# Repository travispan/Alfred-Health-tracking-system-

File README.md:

# Alfred: Health Information tracking system (final year design project)

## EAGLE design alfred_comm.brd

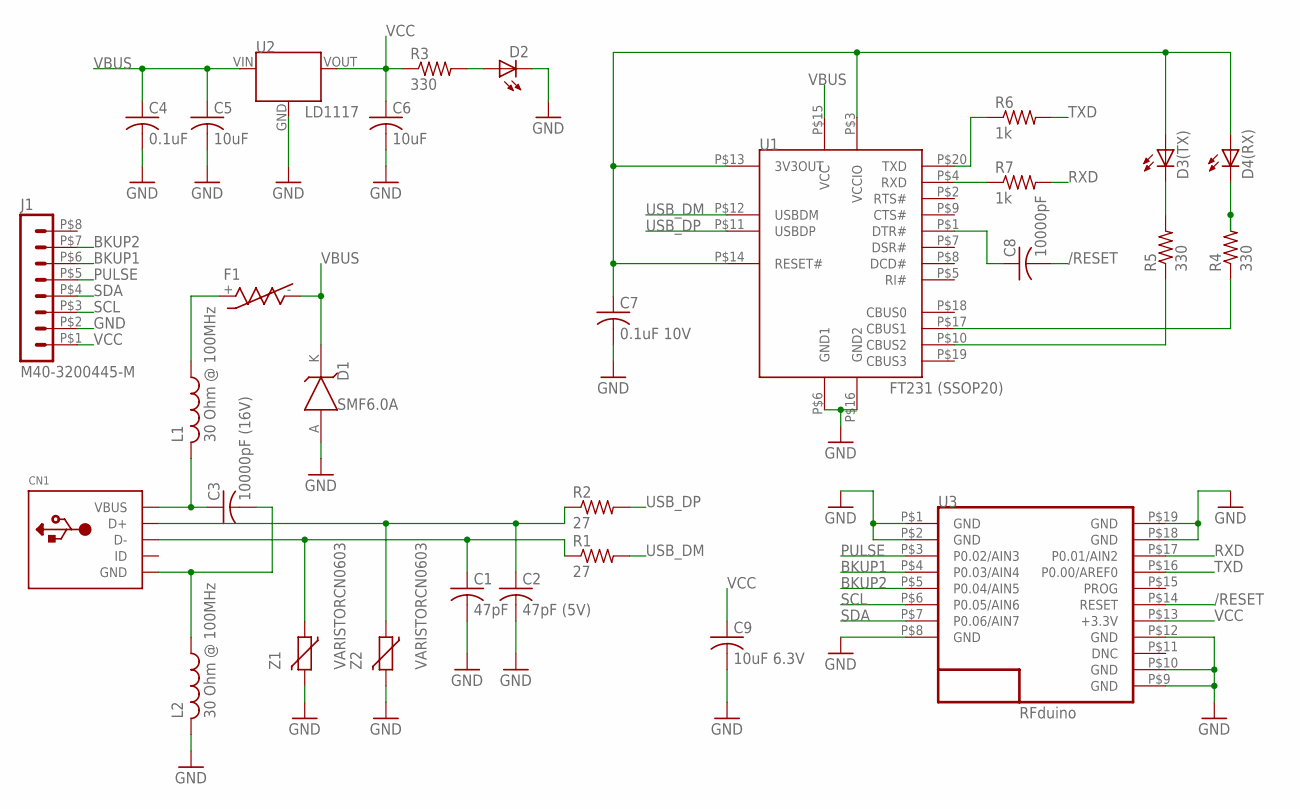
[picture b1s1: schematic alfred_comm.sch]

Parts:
C1: 47pF; C0603
C2: 47pF (5V); C0603
C3: 10000pF (16V); C0603
C4: 0.1uF; C0603
C5, C6: 10uF; C0603
C7: 0.1uF 10V; C0603
C8: 10000pF; C0603
C9: 10uF 6.3V; C0603
CN1: USBMINIB; USB-MINIB
D1: SMF6.0A; SOD-123F
D2, D3(TX), D4(RX): LEDCHIPLED_0603; CHIPLED_0603
F1: MF-MSMF050; BOURNS-STYLE1
J1: M40-3200445-M; 8-PO-M
L1, L2: 30 Ohm @ 100MHz; L0603
R1, R2: 27; R0603
R3, R4, R5: 330; R0603
R6, R7: 1k; R0603
U1: FT231; SSOP20
U2: LD1117-SOT-223; SOT223
U3: RFD22301; RFD21733
Z1, Z2: VARISTORCN0603; CT/CN0603

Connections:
/RESET: C8.2, U3.P$14 (RESET)
BKUP1: J1.P$6 (6), U3.P$4 (P0.03/AIN4)
BKUP2: J1.P$7 (7), U3.P$5 (P0.04/AIN5)
GND: C1.2, C2.2, C4.2, C5.2, C6.2, C7.2, C9.2, D1.A, D2.C, J1.P$2 (2), L2.2, U1.P$6 (GND1), U1.P$16 (GND2), U2.GND, U3.P$1 (GND), U3.P$2 (GND), U3.P$8 (GND), U3.P$9 (GND), U3.P$10 (GND), U3.P$12 (GND), U3.P$18 (GND), U3.P$19 (GND), Z1.2, Z2.2
unnamed: C2.1, CN1.D+, R2.1, Z2.1
unnamed: C1.1, CN1.D-, R1.1, Z1.1
unnamed: C3.1, CN1.VBUS, L1.2
unnamed: C3.2, CN1.GND, L2.1
unnamed: F1.+, L1.1
unnamed: C7.1, D3(TX).A, D4(RX).A, U1.P$3 (VCCIO), U1.P$13 (3V3OUT), U1.P$14 (RESET#)
unnamed: C8.1, U1.P$1 (DTR#)
unnamed: R4.1, U1.P$17 (CBUS1)
unnamed: D3(TX).C, R5.2
unnamed: D4(RX).C, R4.2
unnamed: R5.1, U1.P$10 (CBUS2)
unnamed: R6.1, U1.P$20 (TXD)
unnamed: R7.1, U1.P$4 (RXD)
unnamed: D2.A, R3.2
PULSE: J1.P$5 (5), U3.P$3 (P0.02/AIN3)
RXD: R7.2, U3.P$17 (P0.01/AIN2)
SCL: J1.P$3 (3), U3.P$6 (P0.05/AIN6)
SDA: J1.P$4 (4), U3.P$7 (P0.06/AIN7)
TXD: R6.2, U3.P$16 (P0.00/AREF0)
USB_DM: R1.2, U1.P$12 (USBDM)
USB_DP: R2.2, U1.P$11 (USBDP)
VBUS: C4.1, C5.1, D1.K, F1.-, U1.P$15 (VCC), U2.VIN (IN)
VCC: C6.1, C9.1, J1.P$1 (1), R3.1, U2.VOUT (OUT), U3.P$13 (+3.3V)

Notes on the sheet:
RFduino
FT231 (SSOP20)
LD1117
SMF6.0A

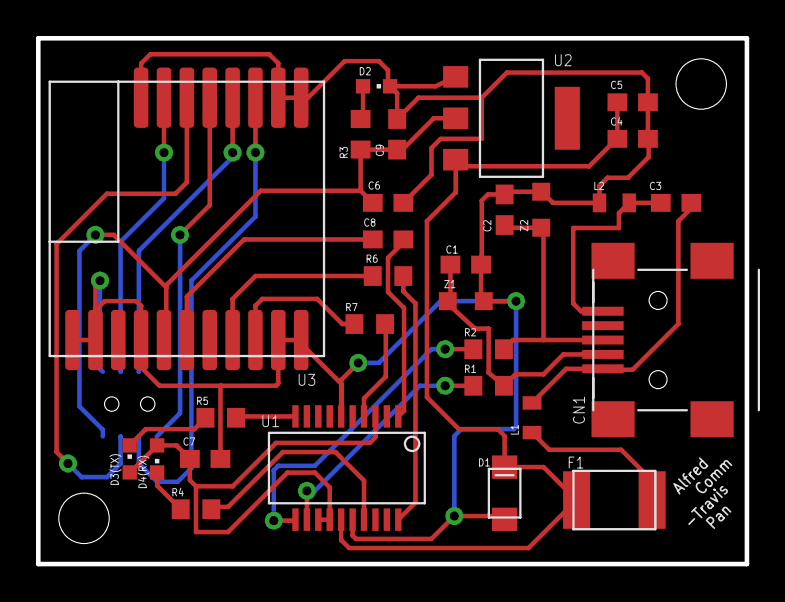
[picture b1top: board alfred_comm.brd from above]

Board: 2 copper layers, 39.4 x 29.2 mm, 30 parts (1 on the bottom side), 27 nets.

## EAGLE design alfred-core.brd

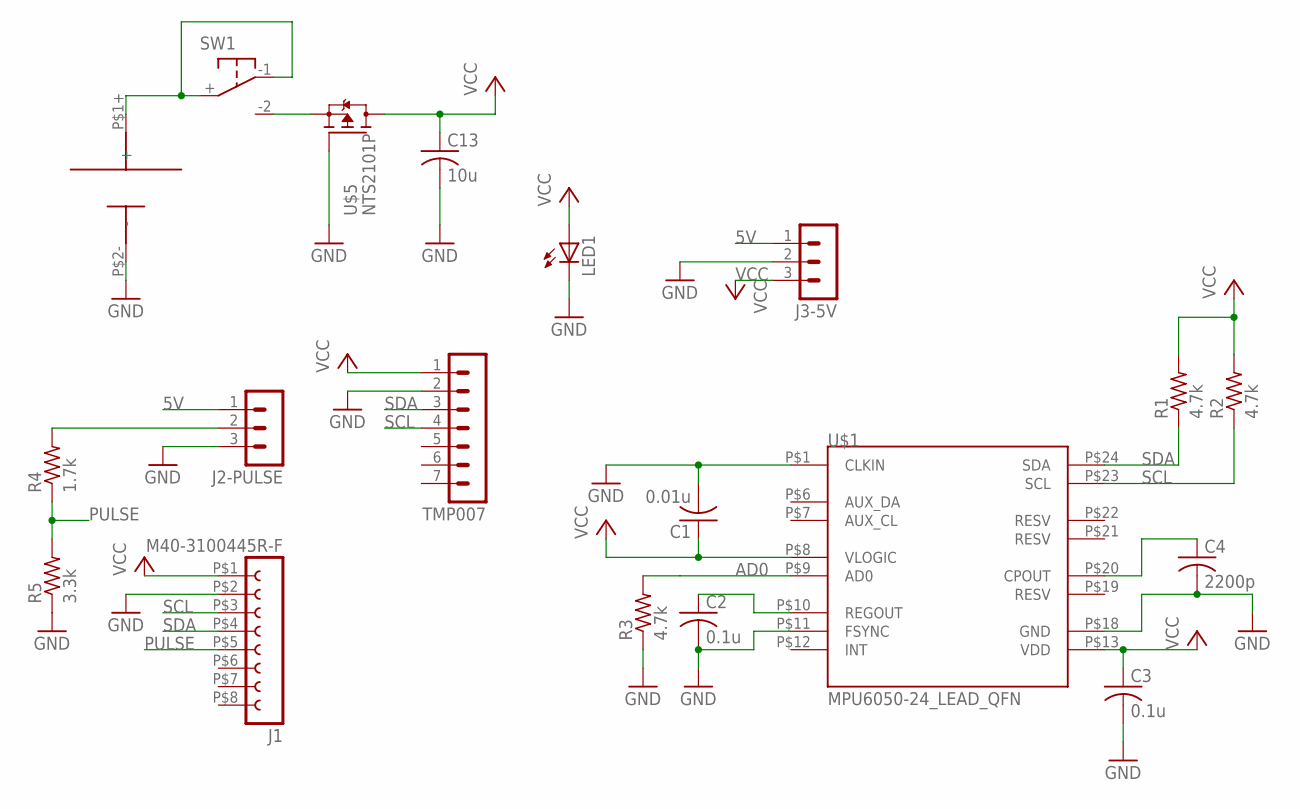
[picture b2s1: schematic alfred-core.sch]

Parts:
BAT1: CR2032HOLDER; CR2032-HOLDER
C1: 0.01u; C0603
C2, C3: 0.1u; C0603
C4: 2200p; C0603
C13: 10u; C0603
J1: M40-3100445R-F; 8-PO-F
J2-PULSE, J3-5V: MA03-1
LED1: LEDCHIPLED_0603; CHIPLED_0603
R1, R2, R3: 4.7k; R0603
R4: 1.7k; R0603
R5: 3.3k; R0603
SW1: JS102011SAQN
TMP007: MA07-1
U$1: MPU6050-24_LEAD_QFN; 24_LEAD_QFN(4X4X0.9)
U$5: NTS2101P; SOT323

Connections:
5V: J2-PULSE.1, J3-5V.1
AD0: R3.2, U$1.P$9 (AD0)
GND: BAT1.P$2- (-), C1.2, C2.2, C3.2, C4.2, C13.2, J1.P$2 (2), J2-PULSE.3, J3-5V.2, LED1.C, R3.1, R5.1, TMP007.2, U$1.P$1 (CLKIN), U$1.P$11 (FSYNC), U$1.P$18 (GND), U$5.G
unnamed: C2.1, U$1.P$10 (REGOUT)
unnamed: C4.1, U$1.P$20 (CPOUT)
unnamed: J2-PULSE.2, R4.2
unnamed: BAT1.P$1+ (+), SW1.+, SW1.-1
unnamed: SW1.-2, U$5.S
PULSE: J1.P$5 (5), R4.1, R5.2
SCL: J1.P$3 (3), R2.1, TMP007.4, U$1.P$23 (SCL)
SDA: J1.P$4 (4), R1.1, TMP007.3, U$1.P$24 (SDA)
VCC: C1.1, C3.1, C13.1, J1.P$1 (1), J3-5V.3, LED1.A, R1.2, R2.2, TMP007.1, U$1.P$8 (VLOGIC), U$1.P$13 (VDD), U$5.D

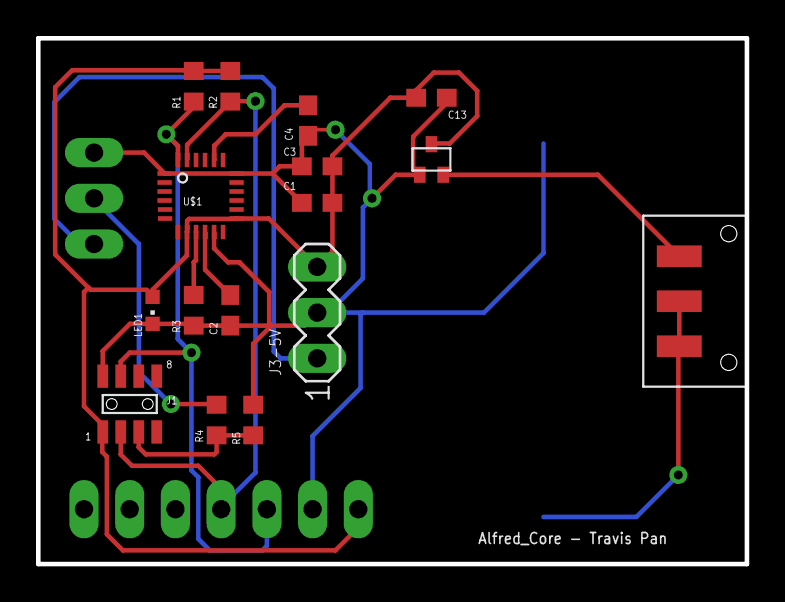
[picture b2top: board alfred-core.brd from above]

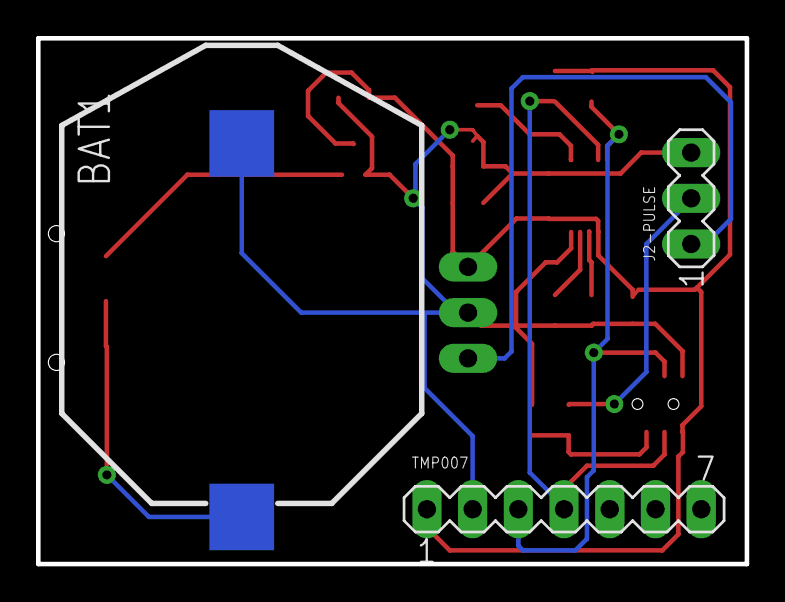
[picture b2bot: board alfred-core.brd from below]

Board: 2 copper layers, 39.4 x 29.2 mm, 19 parts (3 on the bottom side), 12 nets.

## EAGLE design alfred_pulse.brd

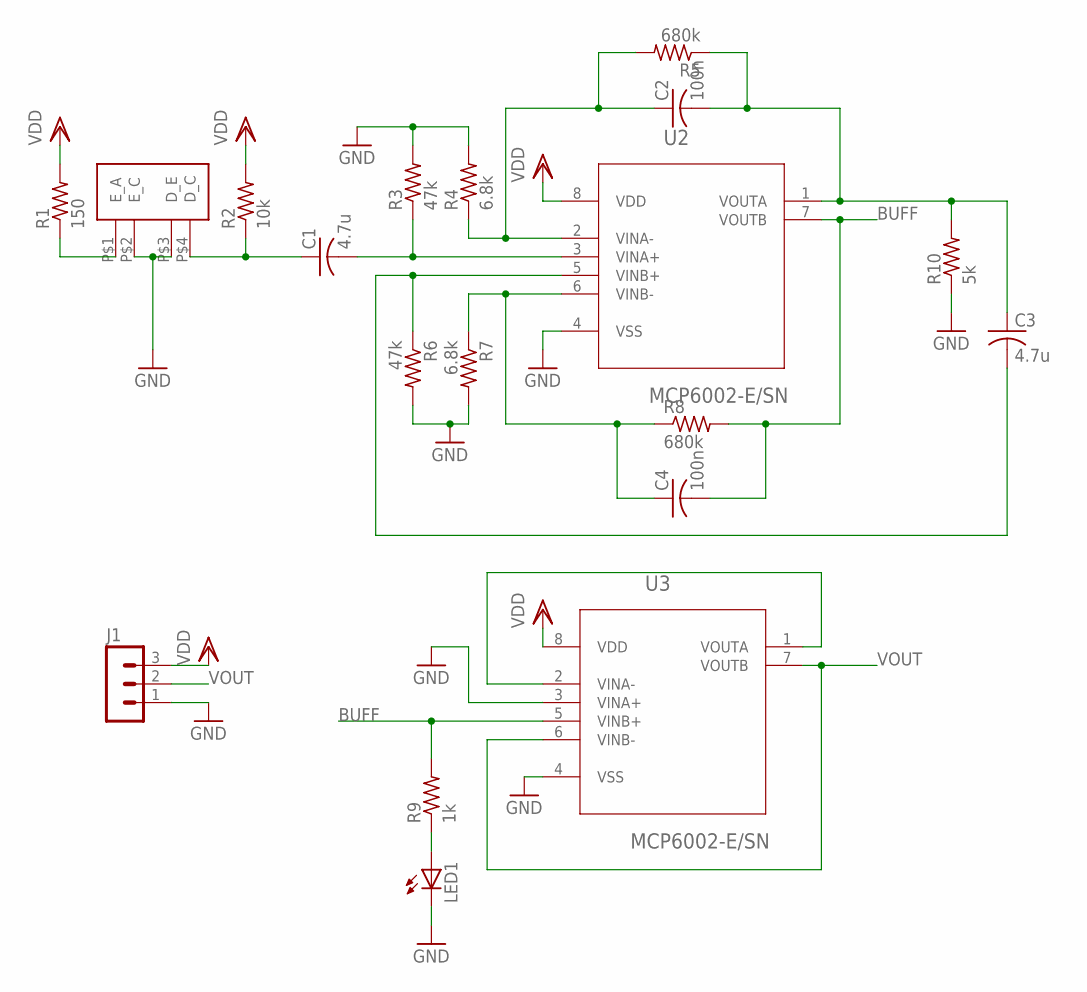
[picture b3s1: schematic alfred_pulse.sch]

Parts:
C1, C3: 4.7u; C0603
C2, C4: 100n; C0603
J1: MA03-1
LED1: LEDCHIPLED_1206; CHIPLED_1206
R1: 150; R0603
R2: 10k; R0603
R3, R6: 47k; R0603
R4, R7: 6.8k; R0603
R5, R8: 680k; R0603
R9: 1k; R0603
R10: 5k; R0603
U2, U3: MCP6002-E/SN; SOIC127P600X175-8N
U$1: TCRT1001

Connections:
BUFF: C4.2, R8.2, R9.2, U2.7 (VOUTB), U3.5 (VINB+)
GND: J1.1, LED1.C, R3.2, R4.2, R6.2, R7.2, R10.1, U2.4 (VSS), U3.3 (VINA+), U3.4 (VSS), U$1.P$2 (E_C), U$1.P$3 (D_E)
unnamed: R1.1, U$1.P$1 (E_A)
unnamed: C1.1, R2.1, U$1.P$4 (D_C)
unnamed: C1.2, R3.1, U2.3 (VINA+)
unnamed: C3.2, R6.1, U2.5 (VINB+)
unnamed: LED1.A, R9.1
unnamed: C4.1, R7.1, R8.1, U2.6 (VINB-)
unnamed: C2.2, C3.1, R5.1, R10.2, U2.1 (VOUTA)
unnamed: C2.1, R4.1, R5.2, U2.2 (VINA-)
unnamed: U3.1 (VOUTA), U3.2 (VINA-)
VDD: J1.3, R1.2, R2.2, U2.8 (VDD), U3.8 (VDD)
VOUT: J1.2, U3.6 (VINB-), U3.7 (VOUTB)

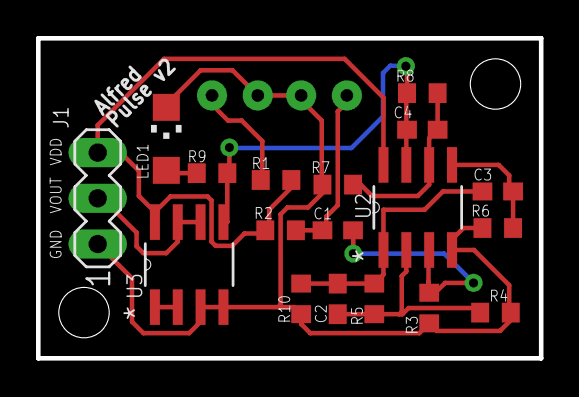
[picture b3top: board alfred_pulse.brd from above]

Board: 2 copper layers, 27.9 x 17.8 mm, 19 parts (1 on the bottom side), 13 nets.

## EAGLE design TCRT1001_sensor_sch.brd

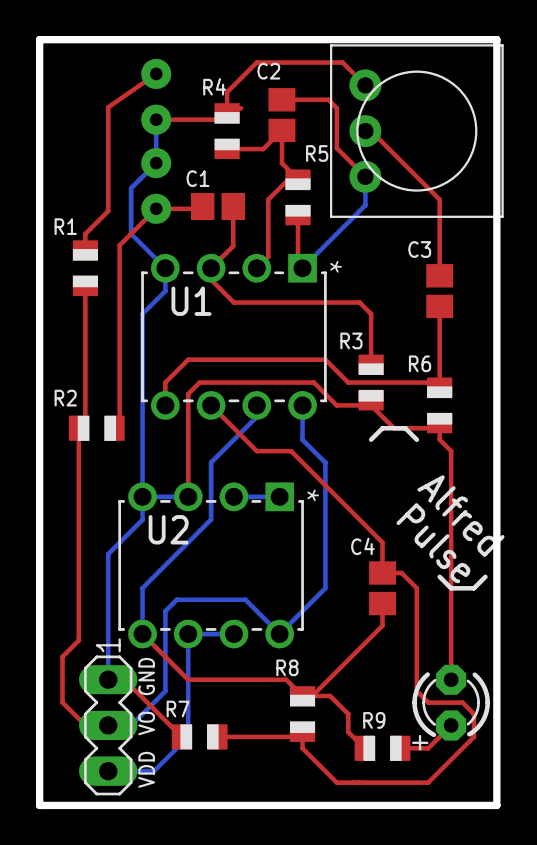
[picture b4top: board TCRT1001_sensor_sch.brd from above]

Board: 2 copper layers, 25.4 x 42.5 mm, 19 parts (1 on the bottom side), 14 nets.

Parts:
C1, C3: 4.7u; C0805
C2, C4: 100n; C0805
LED1: LED3MM
R1: 150; R0805
R2: 10k; R0805
R3, R6: 47k; R0805
R4, R7: 6.8k; R0805
R5, R8: 680k; R0805
R9: 1k; R0805
SV1: MA03-1
TM1: TRIM-3386
U1, U2: MCP6002-I/P; DIP254P762X533-8
U$1: TCRT1001

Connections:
BUFF: C4.2, R8.1, R9.2, U1.7, U2.5
GND: LED1.K, R3.2, R4.2, R6.1, R7.1, SV1.1, TM1.1, U1.4, U2.3, U2.4, U$1.P$2, U$1.P$3
unnamed: R1.1, U$1.P$1
unnamed: C1.1, R2.1, U$1.P$4
unnamed: C1.2, R3.1, U1.3
unnamed: C2.1, R4.1, R5.2, U1.2
unnamed: C2.2, R5.1, TM1.3, U1.1
unnamed: C3.1, TM1.2
unnamed: C3.2, R6.2, U1.5
unnamed: LED1.A, R9.1
unnamed: C4.1, R7.2, R8.2, U1.6
unnamed: U2.1, U2.2
VDD: R1.2, R2.2, SV1.2, U1.8, U2.8
VOUT: SV1.3, U2.6, U2.7

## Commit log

2015-12-16 :circus_tent: Added .gitattributes & .gitignore files
2015-12-16 Adding schematics and boards
2015-12-28 library file for tcrt1001
2015-12-28 second version of the pulse sensor
    size is reduced down to 1.1x0.7 inch. will be used for final prototype
    if it passes test
2015-12-28 hand soldered PCB
2016-01-20 add preview picts
2016-03-09 Added files via upload
2016-04-11 Merging all components to one folder
